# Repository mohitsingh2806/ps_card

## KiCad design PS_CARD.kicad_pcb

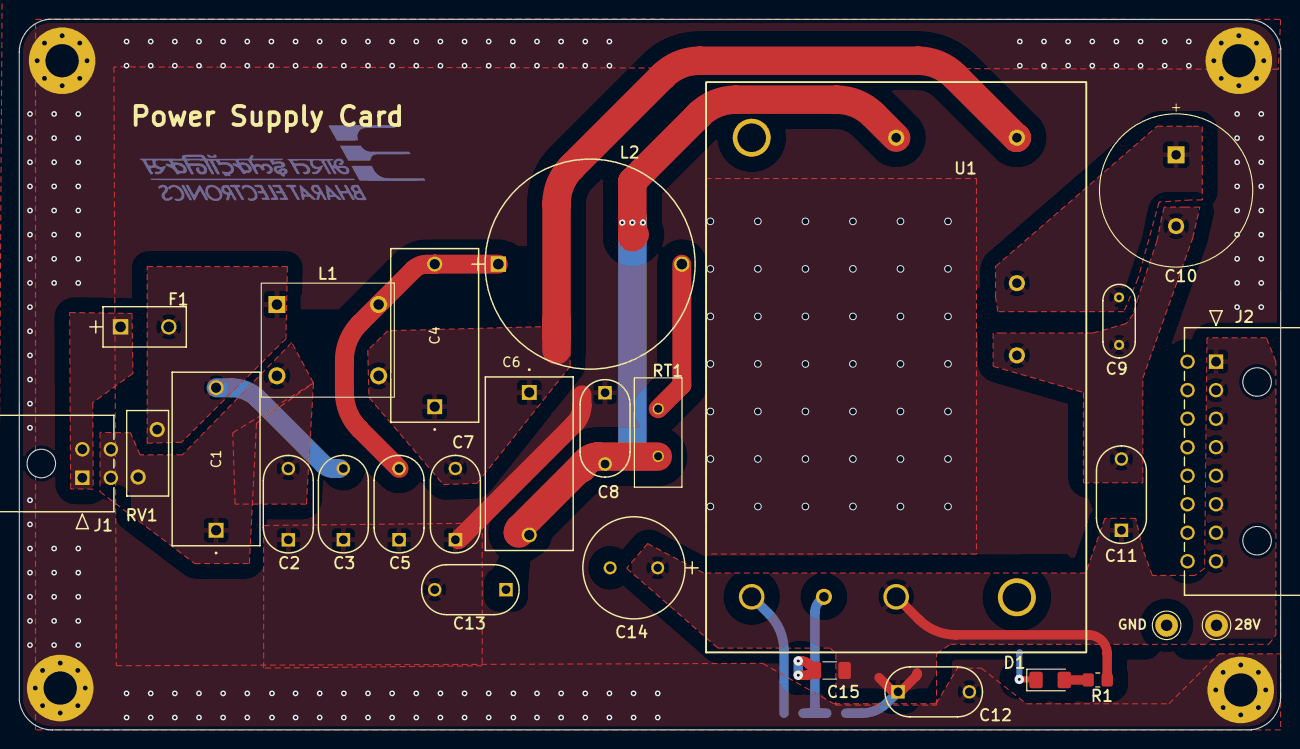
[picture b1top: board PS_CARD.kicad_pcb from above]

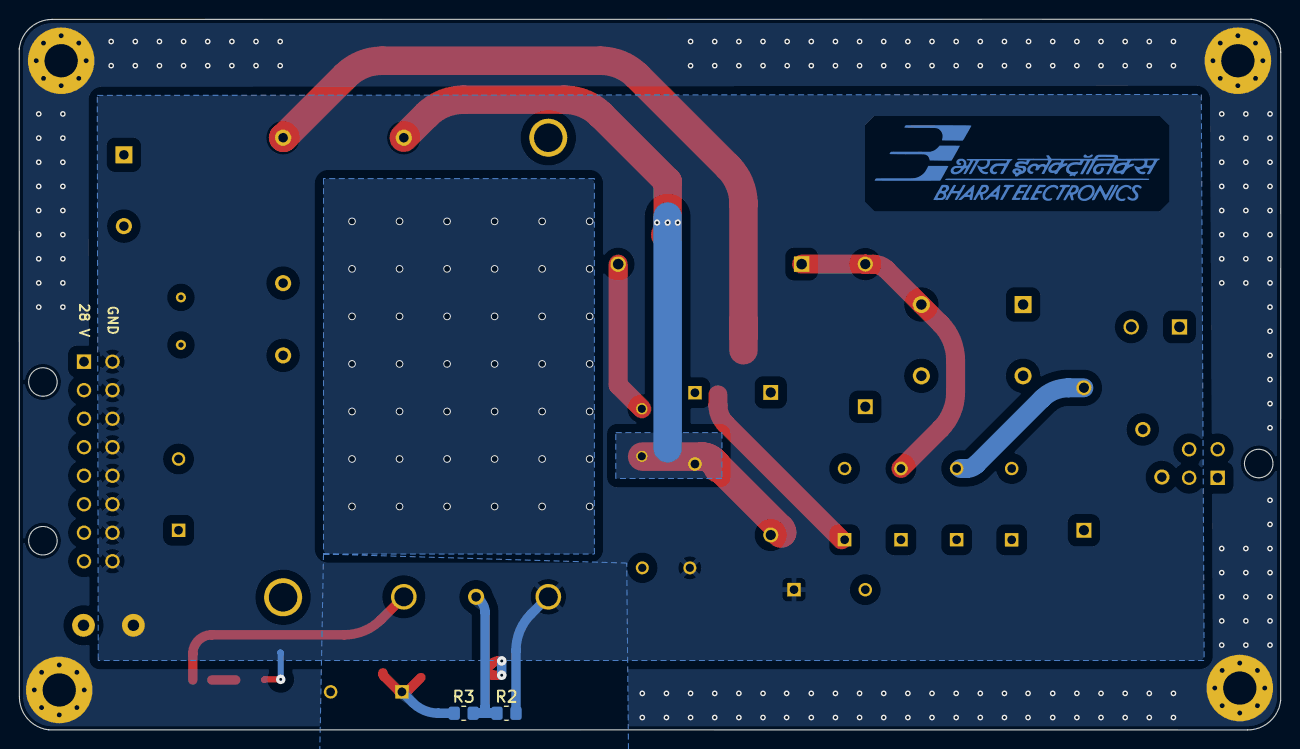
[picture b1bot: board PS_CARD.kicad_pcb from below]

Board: 2 copper layers, 132.7 x 74.8 mm, 33 parts (3 on the bottom side), 14 nets.

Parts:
C1, C4, C6: B32922C3474K; CAP_B32922C3474K000_TDK
C2, C3, C5, C7, C8: DE2E3SA472MA3BX02F; CAP_DE2E3KY472MB3BM02F_MUR
C9: RDER72J104K8K1C11B; R-8K1_MUR
C10: EKXL421ELL121MM30S
C11, C12, C13: DE2E3SA332MA3BX02F; CAP_DE2E3KY472MB3BM02F_MUR
C14: 50ZLH220MEFC10X16; CAP_YX_10X16_RUB
C15: GRJ31CR72A105KE11L; C_1206_3216Metric_Pad1.33x1.80mm_HandSolder
D1: SM1206URC; LED_1206_3216Metric_Pad1.42x1.75mm_HandSolder
F1: 39213150000; FUS_LITTELFUSE_392_LTF
J1: 430450402; 430450402_MOL
J2: 430451602; CON_430451602_MOL
L1: 744823220
L2: 2100LL-560-H-RC; IND_2100LL_34_H
MH1, MH2, MH3, MH4: MountingHole_Pad; MountingHole_3.5mm_Pad_Via
R1: 2.2K; R_0805_2012Metric_Pad1.20x1.40mm_HandSolder
R2, R3: DNP; R_0805_2012Metric_Pad1.20x1.40mm_HandSolder
RT1: B57236S0509M054; THRMRB500W60L1150T500H1600
RV1: MOV-10D621K; RV_Disc_D9mm_W4.4mm_P5mm
TP1, TP2: TestPoint; Pin_D1.0mm_L10.0mm_LooseFit
U1: ACQ100

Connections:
+28V: C11.1, C12.1, C14.1, C15.2, J2.1, J2.2, J2.3, J2.4, J2.5, J2.6, J2.7, J2.8, R1.1, R3.2, TP1.1, U1.5 (+VO)
/ACL: C1.1, C2.2, J1.3, J1.4, L1.2, RV1.2
/ACN: F1.1, J1.1, J1.2
/ACN_FuseToChoke: C1.2, C3.2, F1.2, L1.1, RV1.1
/BoostN: C9.2, C10.2, C11.2, U1.4 (BC-)
/BoostP: C9.1, C10.1, U1.3 (BC+)
/Trim: R2.2, R3.1, U1.6 (Trim)
/U1-AC2: C4.1, C6.1, C7.2, L1.3, U1.2 (AC2)
GND: C13.1, C14.2, C15.1, D1.1 (K), J2.9, J2.10, J2.11, J2.12, J2.13, J2.14, J2.15, J2.16, R2.1, TP2.1, U1.7 (-VO)
GNDPWR: C2.1, C3.1, C5.1, C7.1, C8.1, C12.2, C13.2, MH1.1, MH2.1, MH3.1, MH4.1
unnamed: C4.2, C5.2, L1.4, L2.1
unnamed: D1.2 (A), R1.2
unnamed: L2.2, RT1.1
unnamed: C6.2, C8.2, RT1.2, U1.1 (AC1)

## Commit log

2024-11-26 edied gitignore
2024-11-26 Remove files from tracking
2024-11-26 final changes to gitignore
2024-11-26 Shifted the connector
2024-11-27 Added stiching vias, changed constraints as per MIL275
2024-11-27 Dont Knw
2024-11-27 repositioned silk screen(MINOR)
